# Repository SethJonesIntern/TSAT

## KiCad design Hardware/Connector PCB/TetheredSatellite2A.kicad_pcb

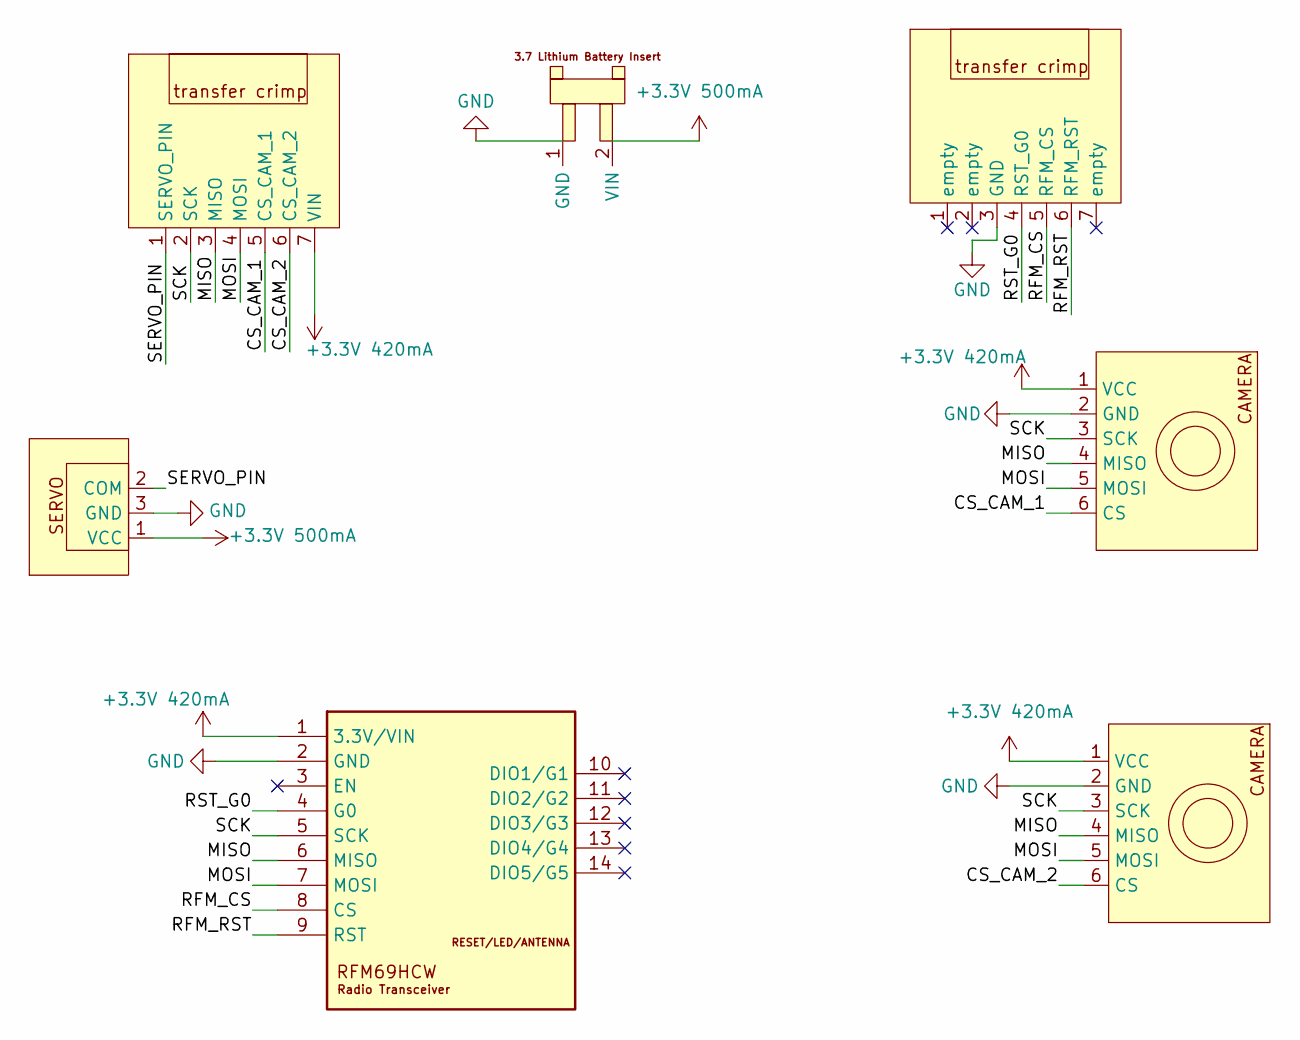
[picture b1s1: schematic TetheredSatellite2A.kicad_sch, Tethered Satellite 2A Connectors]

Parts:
U1: 3.7 Lithium Battery Insert
U2, U6: cameraCONNECTOR
U3: servo
U4, U5: Crimp
h1: RFM69HCW

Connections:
+3.3V 420mA: U2.1 (VCC), U4.7 (VIN), U6.1 (VCC), h1.1 (3.3V/VIN)
+3.3V 500mA: U1.2 (VIN), U3.1 (VCC)
/CS_CAM_1: U2.6 (CS), U4.5 (CS_CAM_1)
/CS_CAM_2: U4.6 (CS_CAM_2), U6.6 (CS)
/MISO: U2.4 (MISO), U4.3 (MISO), U6.4 (MISO), h1.6 (MISO)
/MOSI: U2.5 (MOSI), U4.4 (MOSI), U6.5 (MOSI), h1.7 (MOSI)
/RFM_CS: U5.5 (RFM_CS), h1.8 (CS)
/RFM_RST: U5.6 (RFM_RST), h1.9 (RST)
/RST_G0: U5.4 (RST_G0), h1.4 (G0)
/SCK: U2.3 (SCK), U4.2 (SCK), U6.3 (SCK), h1.5 (SCK)
/SERVO_PIN: U3.2 (COM), U4.1 (SERVO_PIN)
GND: U1.1 (GND), U2.2 (GND), U3.3 (GND), U5.3 (GND), U6.2 (GND), h1.2 (GND)

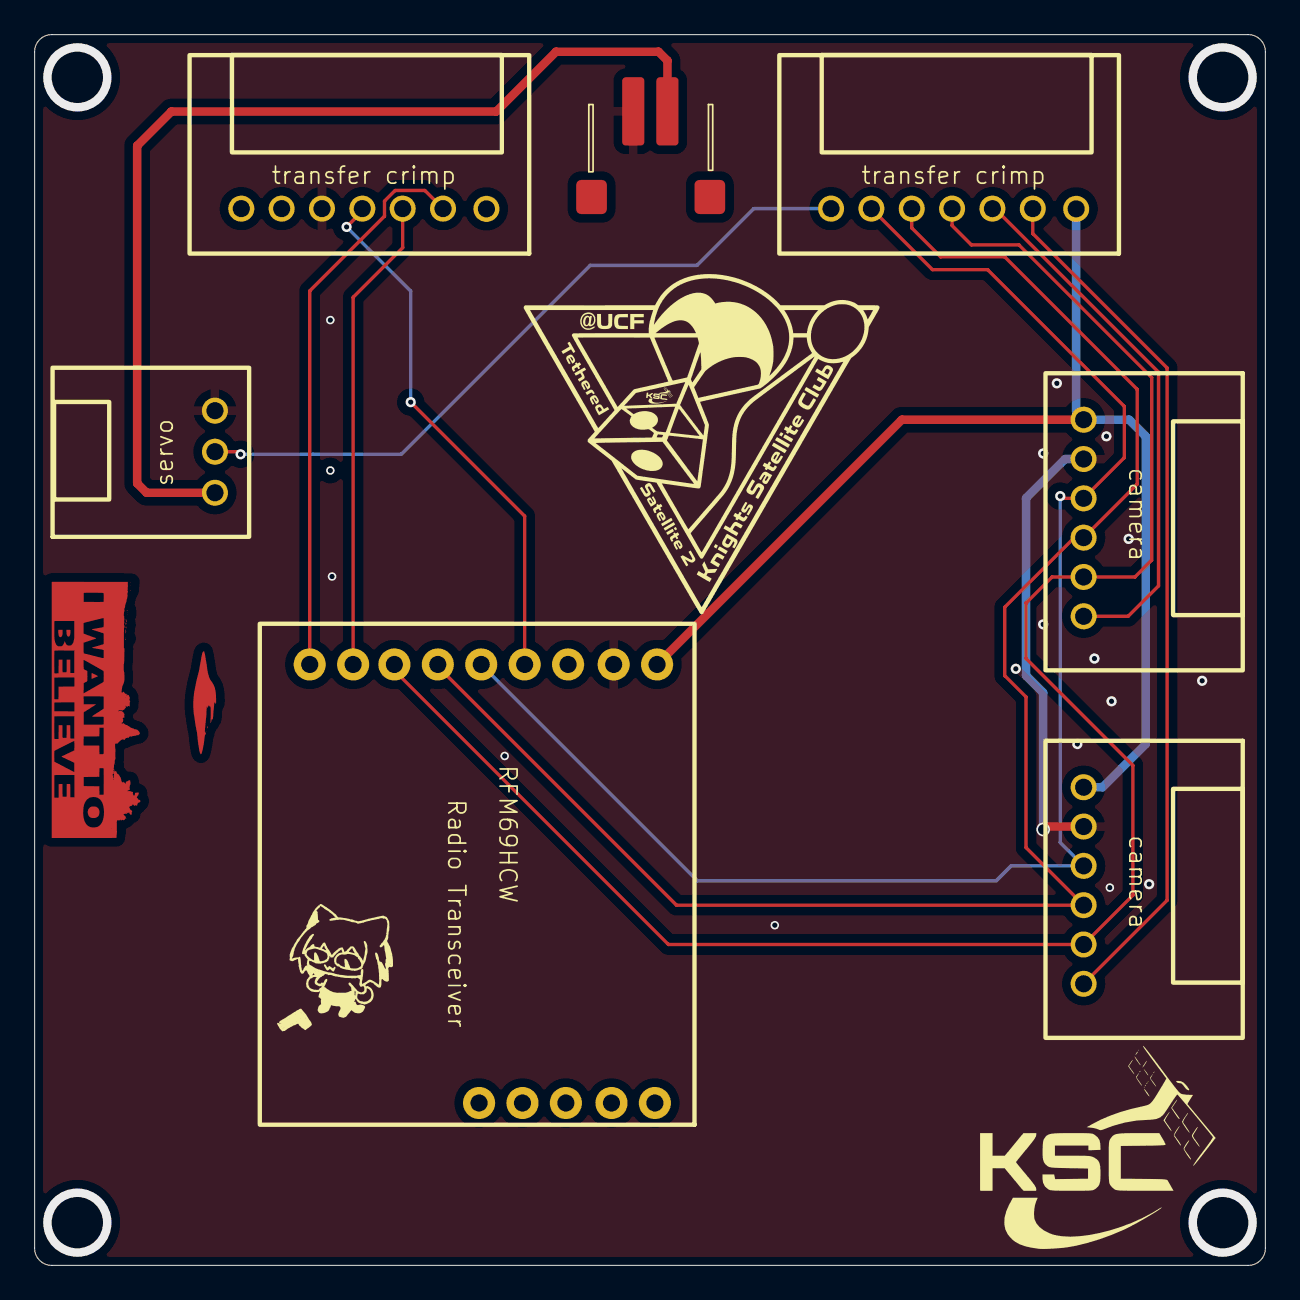
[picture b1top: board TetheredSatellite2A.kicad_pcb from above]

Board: 2 copper layers, 72.0 x 72.0 mm, 7 parts (0 on the bottom side), 12 nets.

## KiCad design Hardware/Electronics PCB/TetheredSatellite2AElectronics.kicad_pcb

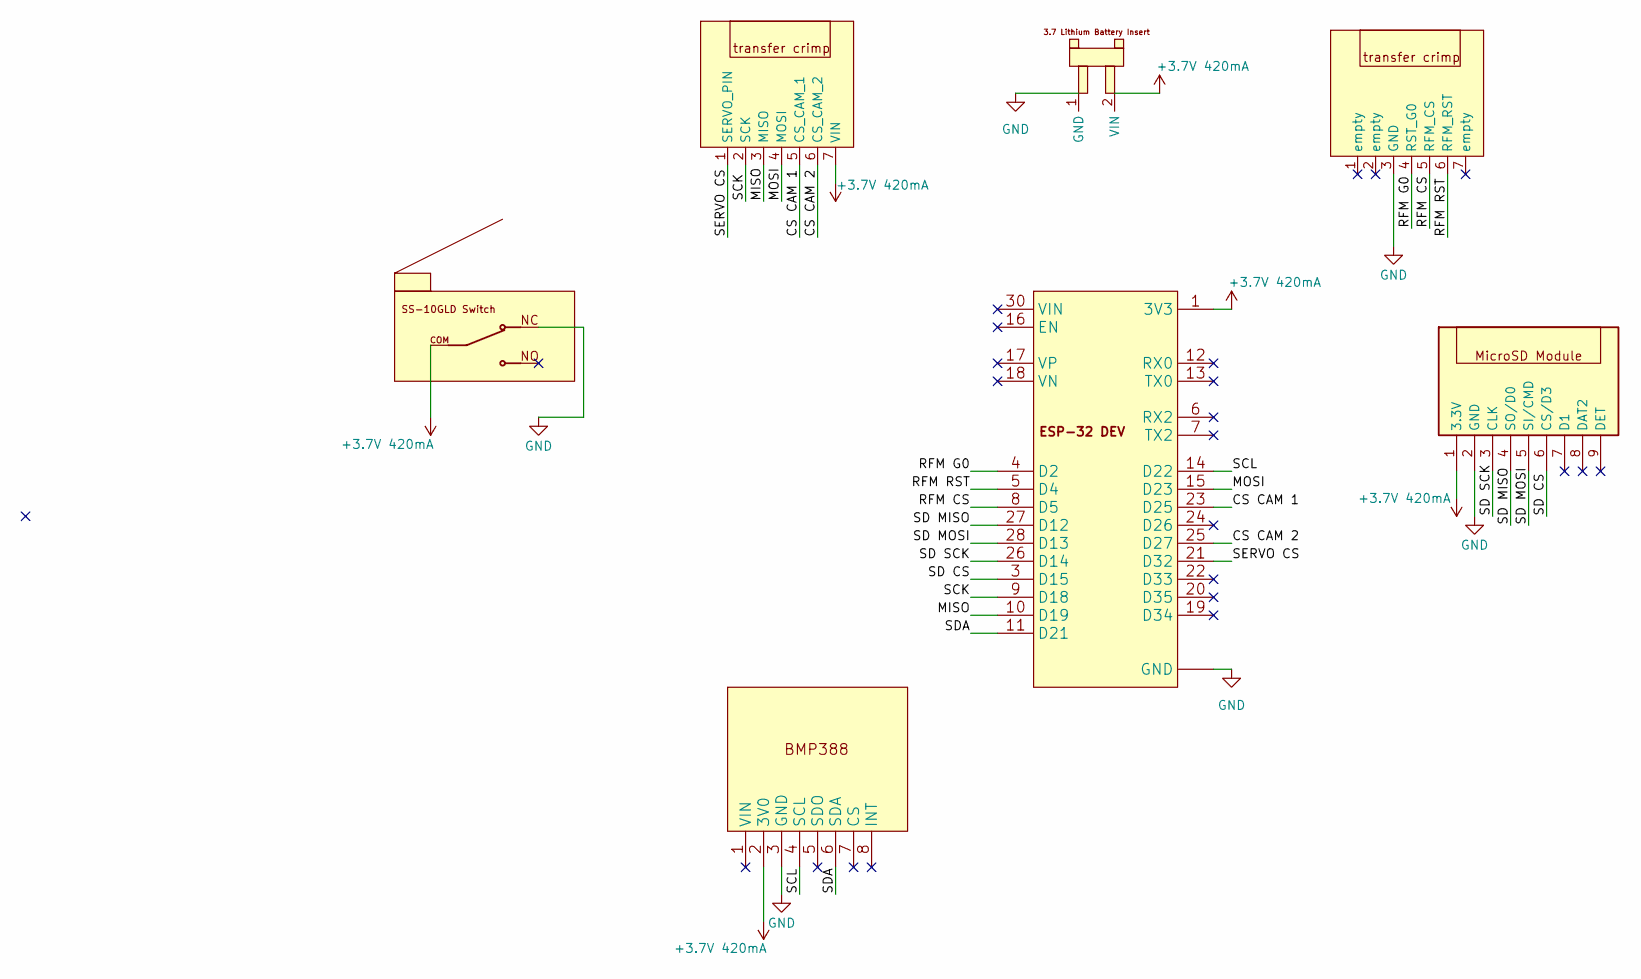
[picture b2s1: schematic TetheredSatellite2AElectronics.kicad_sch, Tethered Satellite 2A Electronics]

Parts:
D1: BMP388
U1: 3.7 Lithium Battery Insert
U2, U3: Crimp
U4: ESP32_DEV
s2: CHOPPEDMIRCOSD MODULE
t1: rectangle_switch

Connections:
+3.7V 420mA: D1.2 (3V0), U1.2 (VIN), U2.7 (VIN), U4.1 (3V3), s2.1 (3.3V), t1.COM
/CS CAM 1: U2.5 (CS_CAM_1), U4.23 (D25)
/CS CAM 2: U2.6 (CS_CAM_2), U4.25 (D27)
/MISO: U2.3 (MISO), U4.10 (D19)
/MOSI: U2.4 (MOSI), U4.15 (D23)
/RFM CS: U3.5 (RFM_CS), U4.8 (D5)
/RFM G0: U3.4 (RST_G0), U4.4 (D2)
/RFM RST: U3.6 (RFM_RST), U4.5 (D4)
/SCK: U2.2 (SCK), U4.9 (D18)
/SCL: D1.4 (SCL), U4.14 (D22)
/SD CS: U4.3 (D15), s2.6 (CS/D3)
/SD MISO: U4.27 (D12), s2.4 (SO/D0)
/SD MOSI: U4.28 (D13), s2.5 (SI/CMD)
/SD SCK: U4.26 (D14), s2.3 (CLK)
/SDA: D1.6 (SDA), U4.11 (D21)
/SERVO CS: U2.1 (SERVO_PIN), U4.21 (D32)
GND: D1.3 (GND), U1.1 (GND), U3.3 (GND), U4.2 (GND), U4.29 (GND), s2.2 (GND), t1.NC

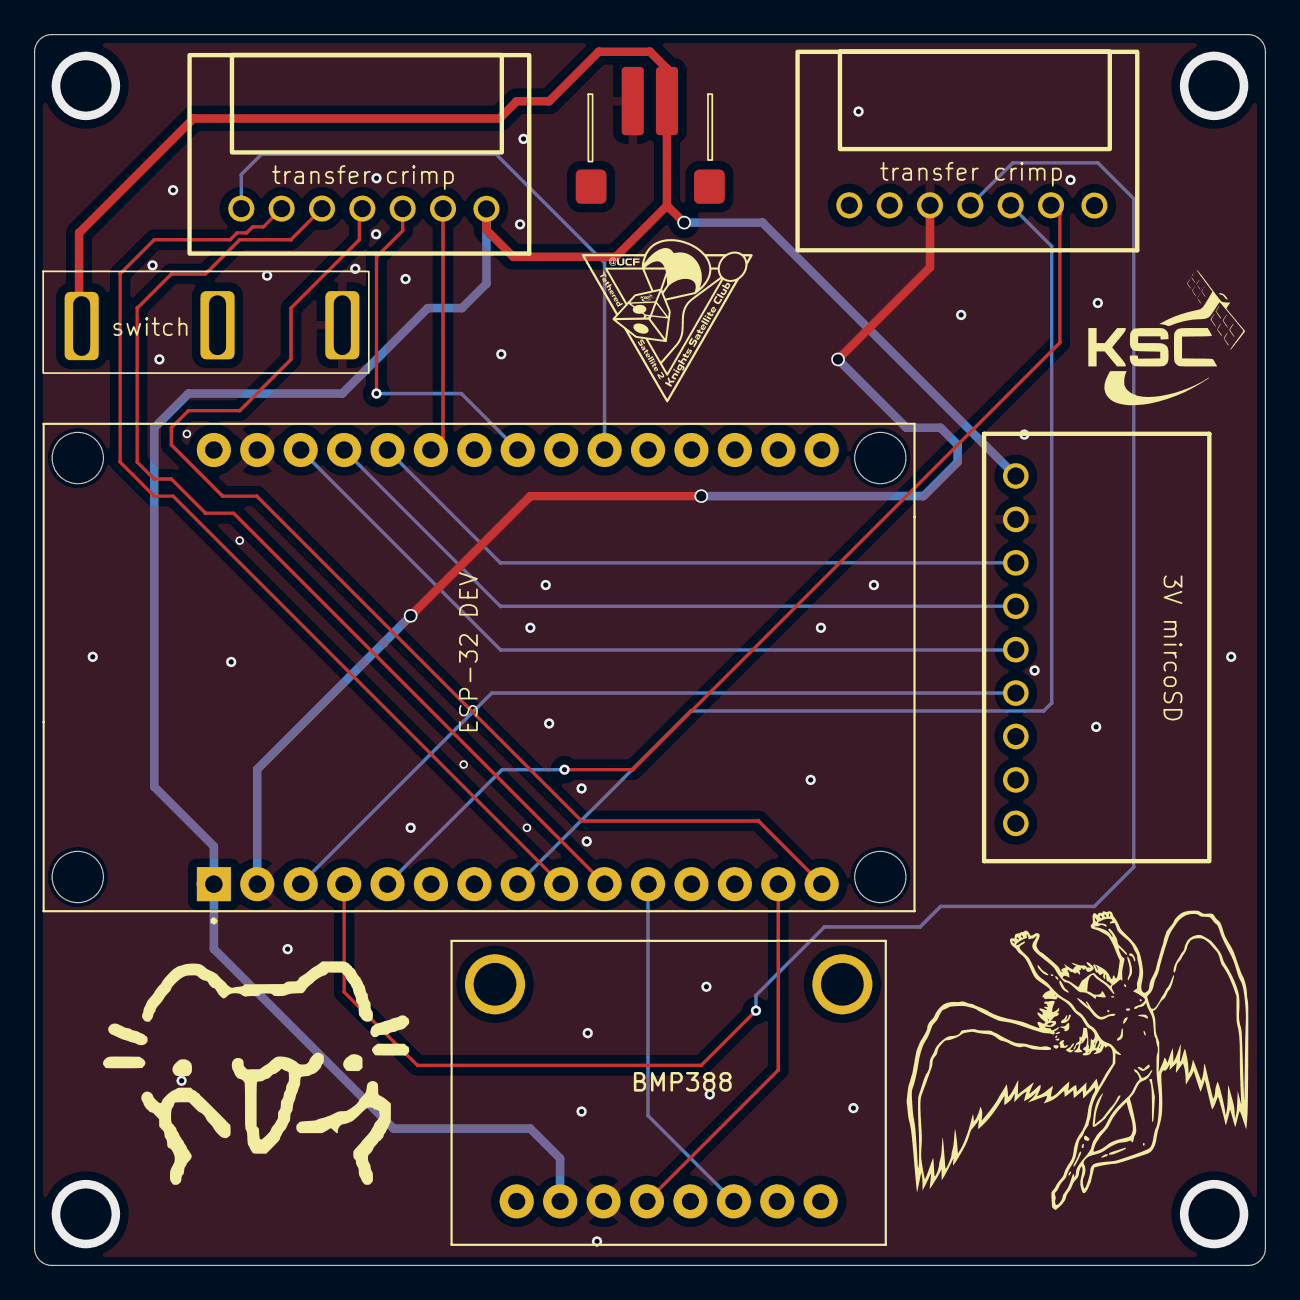
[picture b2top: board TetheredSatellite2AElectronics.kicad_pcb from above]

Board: 2 copper layers, 72.0 x 72.0 mm, 7 parts (0 on the bottom side), 17 nets.

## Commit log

2025-10-07 test
2025-10-09 set test servo correctly
2025-10-14 library inserts and kinda skeleton for camtest
2025-10-16 new lib deps and code skeleton
2025-10-16 camera test code maybe
2025-11-25 added alex's code
2025-11-26 scooby doo
2026-01-23 The best version
2026-01-23 Rename France_CamTest to France_CamTest.cpp
2026-01-30 setup and auxillary functions of skeleton
2026-01-31 Clarify I2C pin connections in BMP388 setup message
    Added clarification on I2C pin connections in the error message.
2026-02-06 changed naming conventions, wrote skele for ground, clarified deliverables on github
2026-02-08 PCB Test Code
2026-02-08 Update PCB_Test.cpp
    Updated to include the RF and Servo
2026-02-08 Update PCB_Test.cpp
    Servo updated functioning
2026-02-08 Add test file in Hardware directory
2026-02-09 Module Wiring Diagram
    This diagram gives an overview of what the wiring should be without inlcuing any specfic pinouts.
2026-02-09 Tethered Satellite 2A Electronics Schematic
    PDF including the first pcb schematic diagram
2026-02-09 Tethered Satellite 2A KICAD schematic
2026-02-09 Create electronics pcb
2026-02-09 Add test file in Electronics PCB directory
2026-02-09 Add test file to Connector PCB directory
2026-02-09 Tethered Satellite 2A Electronics Schematics
    PDF including the first pcb schematic diagram
2026-02-09 Tethered Satellite 2A Electronics RAW Schematic
    RAW KiCAD Schematic
2026-02-09 Tethered Satellite 2A Electronics PCB
    PDF containing PCB view in white and black
2026-02-09 Tethered Satellite 2A Electronics RAW PCB
    RAW KiCAD file for electronics pcb
2026-02-09 Tethered Satellite 2A Connector Schematic
    PDF including the second pcb schematic diagram
2026-02-09 Tethered Satellite 2A RAW Connector Schematic
    RAW KiCAD Connector Schematic
2026-02-09 Tethered Satellite 2A Connector PCB
    PDF containing second PCB view in white and black
2026-02-09 Tethered Satellite 2A Connector RAW PCB
    RAW KiCAD file for connector pcb
2026-02-13 Tethered Satellite 2A Electronics PCB
    PDF containing first PCB view in white and black
2026-02-21 Add symbols file in Symbols & Footprints directory
2026-02-21 Add test file in Symbols directory
2026-02-21 Create test
2026-02-21 3.7 Lithium Battery Insert Symbol
2026-02-21 3.7 Lithium Battery Insert Footprint
2026-02-21 BMP388 Symbol
2026-02-21 BMP388 Footprint
2026-02-21 Camera Symbol
    Used for both Arducam Mega Cameras
2026-02-21 Camera Footprint
    Used for both Arducam Mega Cameras
2026-02-21 MircoSD Module Symbol
    Original mircoSD module got cut so the outline can fit fully in the pcb
2026-02-21 MircoSD Module Footprint
    Original mircoSD module got cut so the outline can fit fully in the pcb
2026-02-21 SS-10GLD Switch Symbol
    This SS-10GLD switch had to have an edited footprint since the pins are rectangular and not circlar like normally is.
2026-02-21 SS-10GLD Switch Footprint
    This SS-10GLD switch had to have an edited footprint since the pins are rectangular and not circlar like normally is.
2026-02-21 Servo Symbol
2026-02-21 Servo Footprint
2026-02-21 Transfer Crimp Empty Symbol
    This transfer crimp has some unused pins making it different from the other one mostly used for pins that go to the RFM module
2026-02-21 Transfer Crimp Footprint
    Both transfer crimps that are used are the same exact insert with just different routing making it different in the symbols
2026-02-21 Transfer Crimp V2 Symbol
    This transfer crimp is different compare to the other with creating routing for the SPI bus and carrying voltage with other task also.
2026-02-21 ESP32 DEV Symbol
2026-02-21 ESP32 DEV Footprint
2026-02-21 RFM69HCW Radio Transceiver Symbol
2026-02-21 RFM69HCW Radio Transceiver Footprint
2026-02-21 Symbols & Footprints ZIP
    This ZIP file contains all the symbols and footprints used in the PCB's their respective folder
2026-03-07 Ground Station Basic Code
    This code contains all the pins that are being used in the ground stationan dthe basic fuction push the button to the servo to release. Most important thing about this code is the pin selections
    ACTION NEEDED TO BE ADDED:
    attiude trabsfered to here with saving through sd card or laptop TBD
    check notes for other actions
2026-03-15 Change sea level pressure constant to 1017.25
    Updated the sea level pressure constant for accuracy.
2026-03-20 added a radio send of altitude
2026-03-20 Change sea level pressure constant to 1017.25
    Updated sea level pressure constant for accuracy.
